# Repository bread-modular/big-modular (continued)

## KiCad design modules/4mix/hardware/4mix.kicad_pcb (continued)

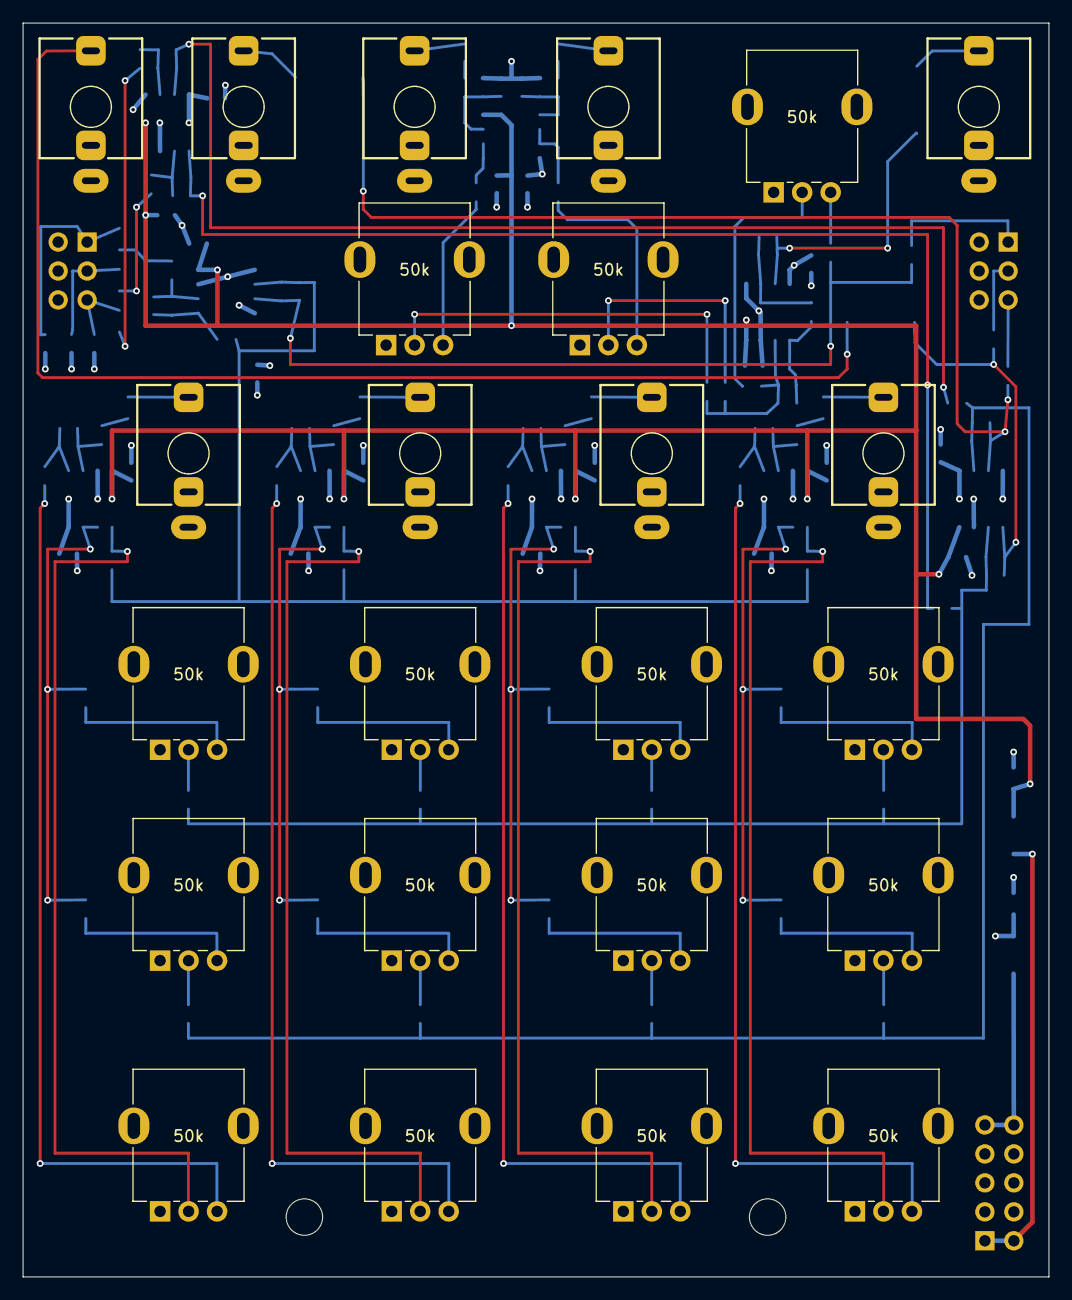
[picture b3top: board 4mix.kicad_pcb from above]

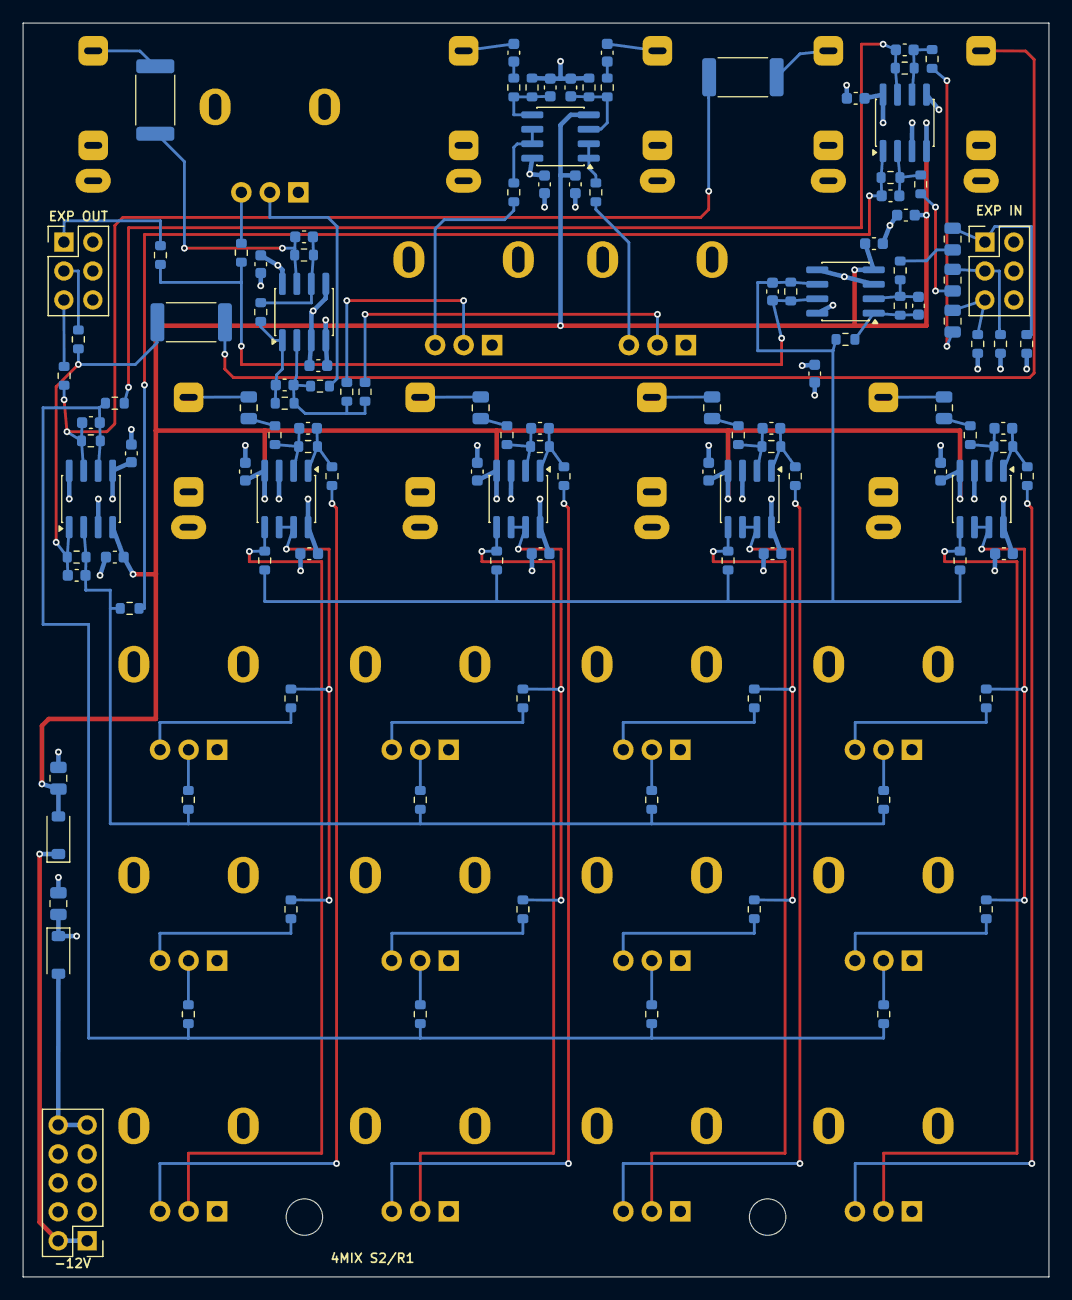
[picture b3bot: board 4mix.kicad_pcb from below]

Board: 4 copper layers, 90.0 x 110.0 mm, 147 parts (123 on the bottom side), 91 nets.
